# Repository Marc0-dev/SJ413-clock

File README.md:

# SJ413-clock
**DISCLAMER** 
The PCB dimensions are approximate, the position of the screw holes is not correct, feel free to contribute in this regard.<br />
You must have the original plastic casing to assemble the clock.<br />
Pointers are much appreciated(i'm still an amateur in electronics).<br />
This project is not complete(it may change and improve in the future).

The project is a replacement of the original suzuki sj-413 dashboard clock. All code on these repository is made using platformIO, leveraging the inexpensive wch ch32v003f4p6 MCU.<br />
List of components(lcsc part numbers):<br />
C1(100nf): C14663, <br />
C2(1uf): C28322, <br />
C3(470uf):C5162352, <br />
C4(330uf):C3032175, <br />
C5(12pf):C76948, <br />
C6(100nf):C14663, <br />
D1:C5357977, <br />
D2:C552776, <br />
J1(oled display connector), <br />
J2(wch-linke interface), <br />
J4(molex connector for rtc), <br />
J5(power connector), <br />
L1(47uh/2A): C5189938, <br />
R1(4k7):C99782, <br />
R2(4k7):C99782, <br />
U1(mcu):C5187096, <br />
U2(buck converter):C2681226, <br />
U3(real time clock):C7440, <br />
Y1:C90945, <br />
display used: C5248081, <br />
# external connection

you should use only the top row of the connector: the left one is positive, the right one is negative
#Images(from previous iteration, without reverse current protection):

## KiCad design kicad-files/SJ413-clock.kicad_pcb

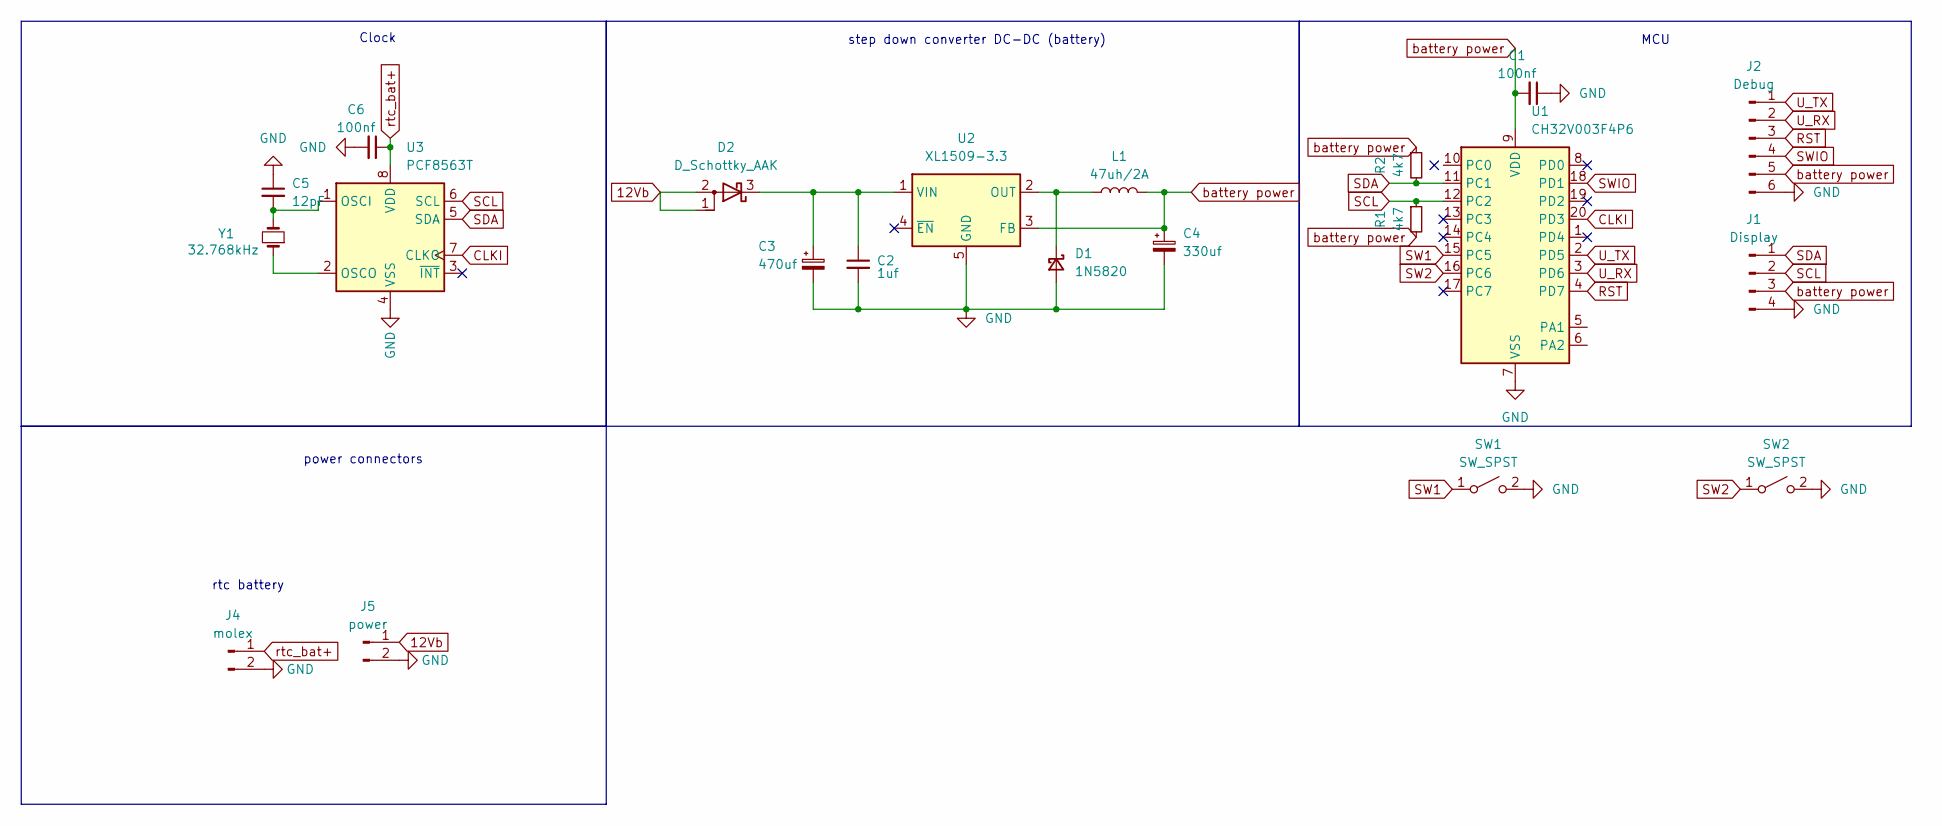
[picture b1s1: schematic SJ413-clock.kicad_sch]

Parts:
C1, C6: 100nf; C_0603_1608Metric; MPN CC0603KRX7R9BB104
C2: 1uf; C_1206_3216Metric
C3: 470uf; CP_Elec_10x10.5
C4: 330uf; CP_Elec_10x10.5
C5: 12pF; C_0402_1005Metric; MPN 0402CG120J500NT
D1: 1N5820; D_DO-201AD_P15.24mm_Horizontal
D2: D_Schottky_AAK; DIO_PMEG050V150EPDZ
J1: Display; PinHeader_1x04_P2.54mm_Vertical_SMD_Pin1Left
J2: Debug; PinSocket_1x06_P2.54mm_Vertical_SMD_Pin1Left
J4: molex; Molex_PicoBlade_53047-0210_1x02_P1.25mm_Vertical
J5: power; PinSocket_1x02_P2.54mm_Vertical_SMD_Pin1Left
L1: 47uh/2A; L_Sumida_CDMC6D28_7.25x6.5mm
R1, R2: 4k7; R_0603_1608Metric
SW1, SW2: SW_SPST; membrane switch
U1: CH32V003F4P6; TSSOP-20_4.4x6.5mm_P0.65mm; MPN CH32V003F4P6
U2: XL1509-3.3; SOIC-8_3.9x4.9mm_P1.27mm
U3: PCF8563T; SOIC-8_3.9x4.9mm_P1.27mm; MPN PCF8563T/5,518
Y1: 32.768kHz; Crystal_SMD_3215-2Pin_3.2x1.5mm; MPN 9H03200034

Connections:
12Vb: D2.1 (A), D2.2 (A), J5.1
CLKI: U1.20 (PD3), U3.7 (CLKO)
GND: C1.1, C2.2, C3.2, C4.2, C5.1, C6.2, D1.2 (A), J1.4, J2.6, J4.2, J5.2, SW1.2 (B), SW2.2 (B), U1.7 (VSS), U2.5 (GND), U2.6 (GND), U2.7 (GND), U2.8 (GND), U3.4 (VSS)
unnamed: D1.1 (K), L1.1, U2.2 (OUT)
unnamed: C2.1, C3.1, D2.3 (K), U2.1 (VIN)
unnamed: C5.2, U3.1 (OSCI), Y1.2
unnamed: U3.2 (OSCO), Y1.1
RST: J2.3, U1.4 (PD7)
SCL: J1.2, R1.1, U1.12 (PC2), U3.6 (SCL)
SDA: J1.1, R2.2, U1.11 (PC1), U3.5 (SDA)
SW1: SW1.1 (A), U1.15 (PC5)
SW2: SW2.1 (A), U1.16 (PC6)
SWIO: J2.4, U1.18 (PD1)
U_RX: J2.2, U1.3 (PD6)
U_TX: J2.1, U1.2 (PD5)
battery power: C1.2, C4.1, J1.3, J2.5, L1.2, R1.2, R2.1, U1.9 (VDD), U2.3 (FB)
rtc_bat+: C6.1, J4.1, U3.8 (VDD)

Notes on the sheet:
MCU
power connectors
Clock
step down converter DC-DC (battery)
rtc battery

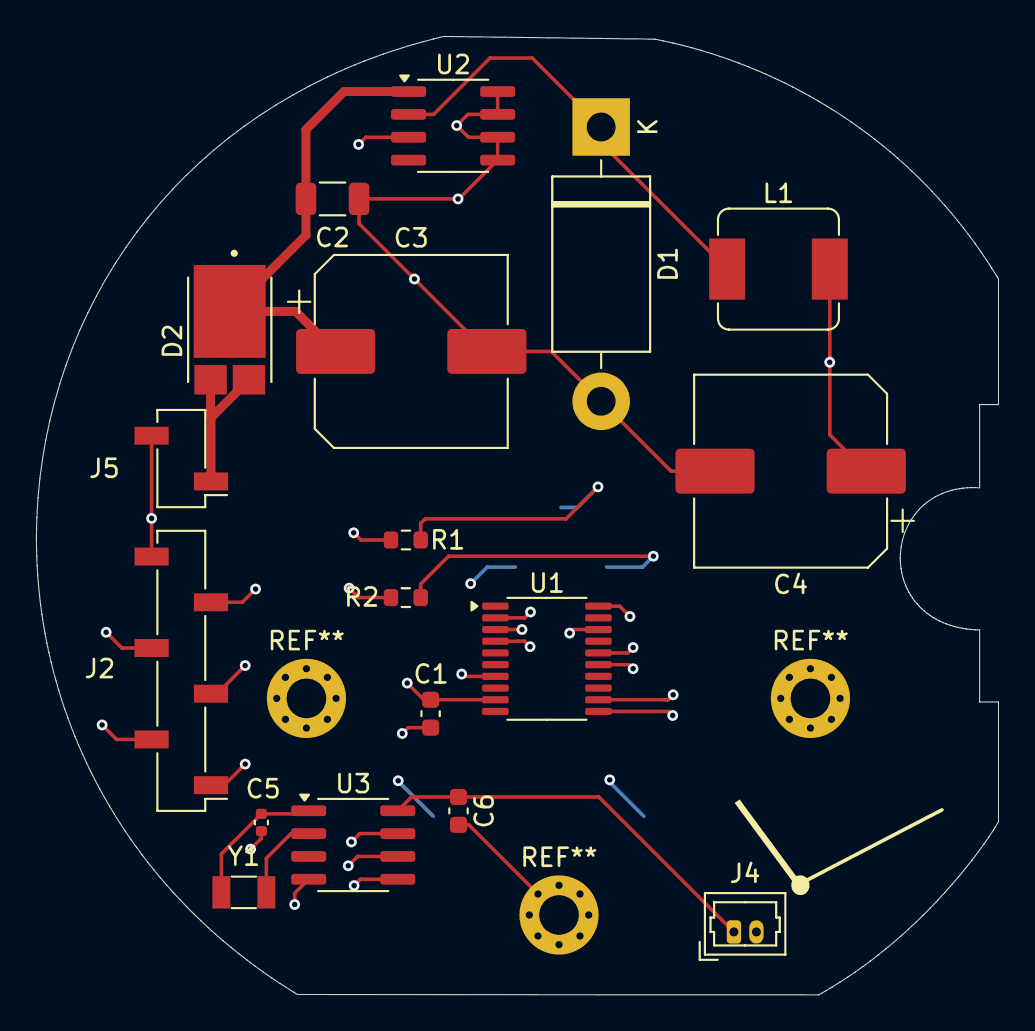
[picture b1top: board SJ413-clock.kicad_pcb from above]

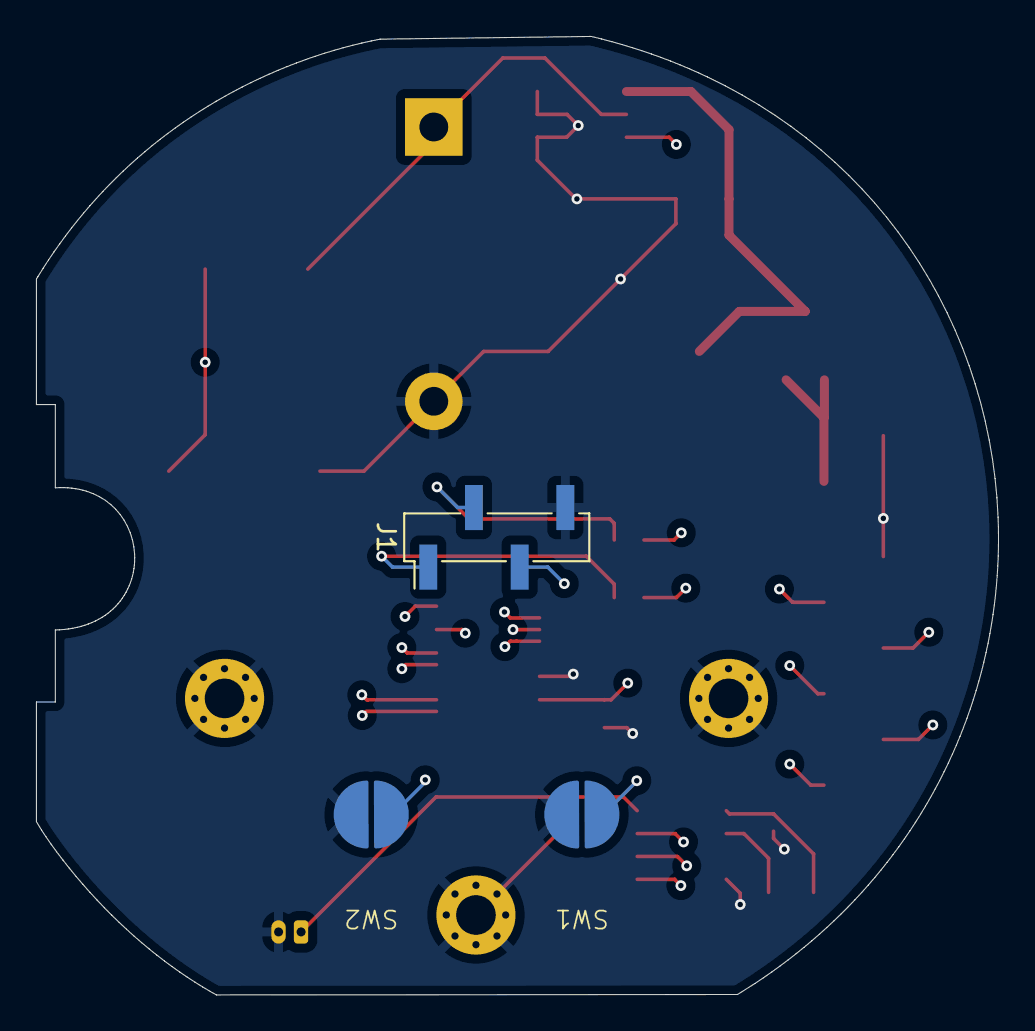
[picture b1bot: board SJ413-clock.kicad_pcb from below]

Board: 4 copper layers, 53.4 x 53.2 mm, 21 parts (3 on the bottom side), 17 nets.

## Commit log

2025-09-19 repository init
2025-09-19 adding platformIO project
